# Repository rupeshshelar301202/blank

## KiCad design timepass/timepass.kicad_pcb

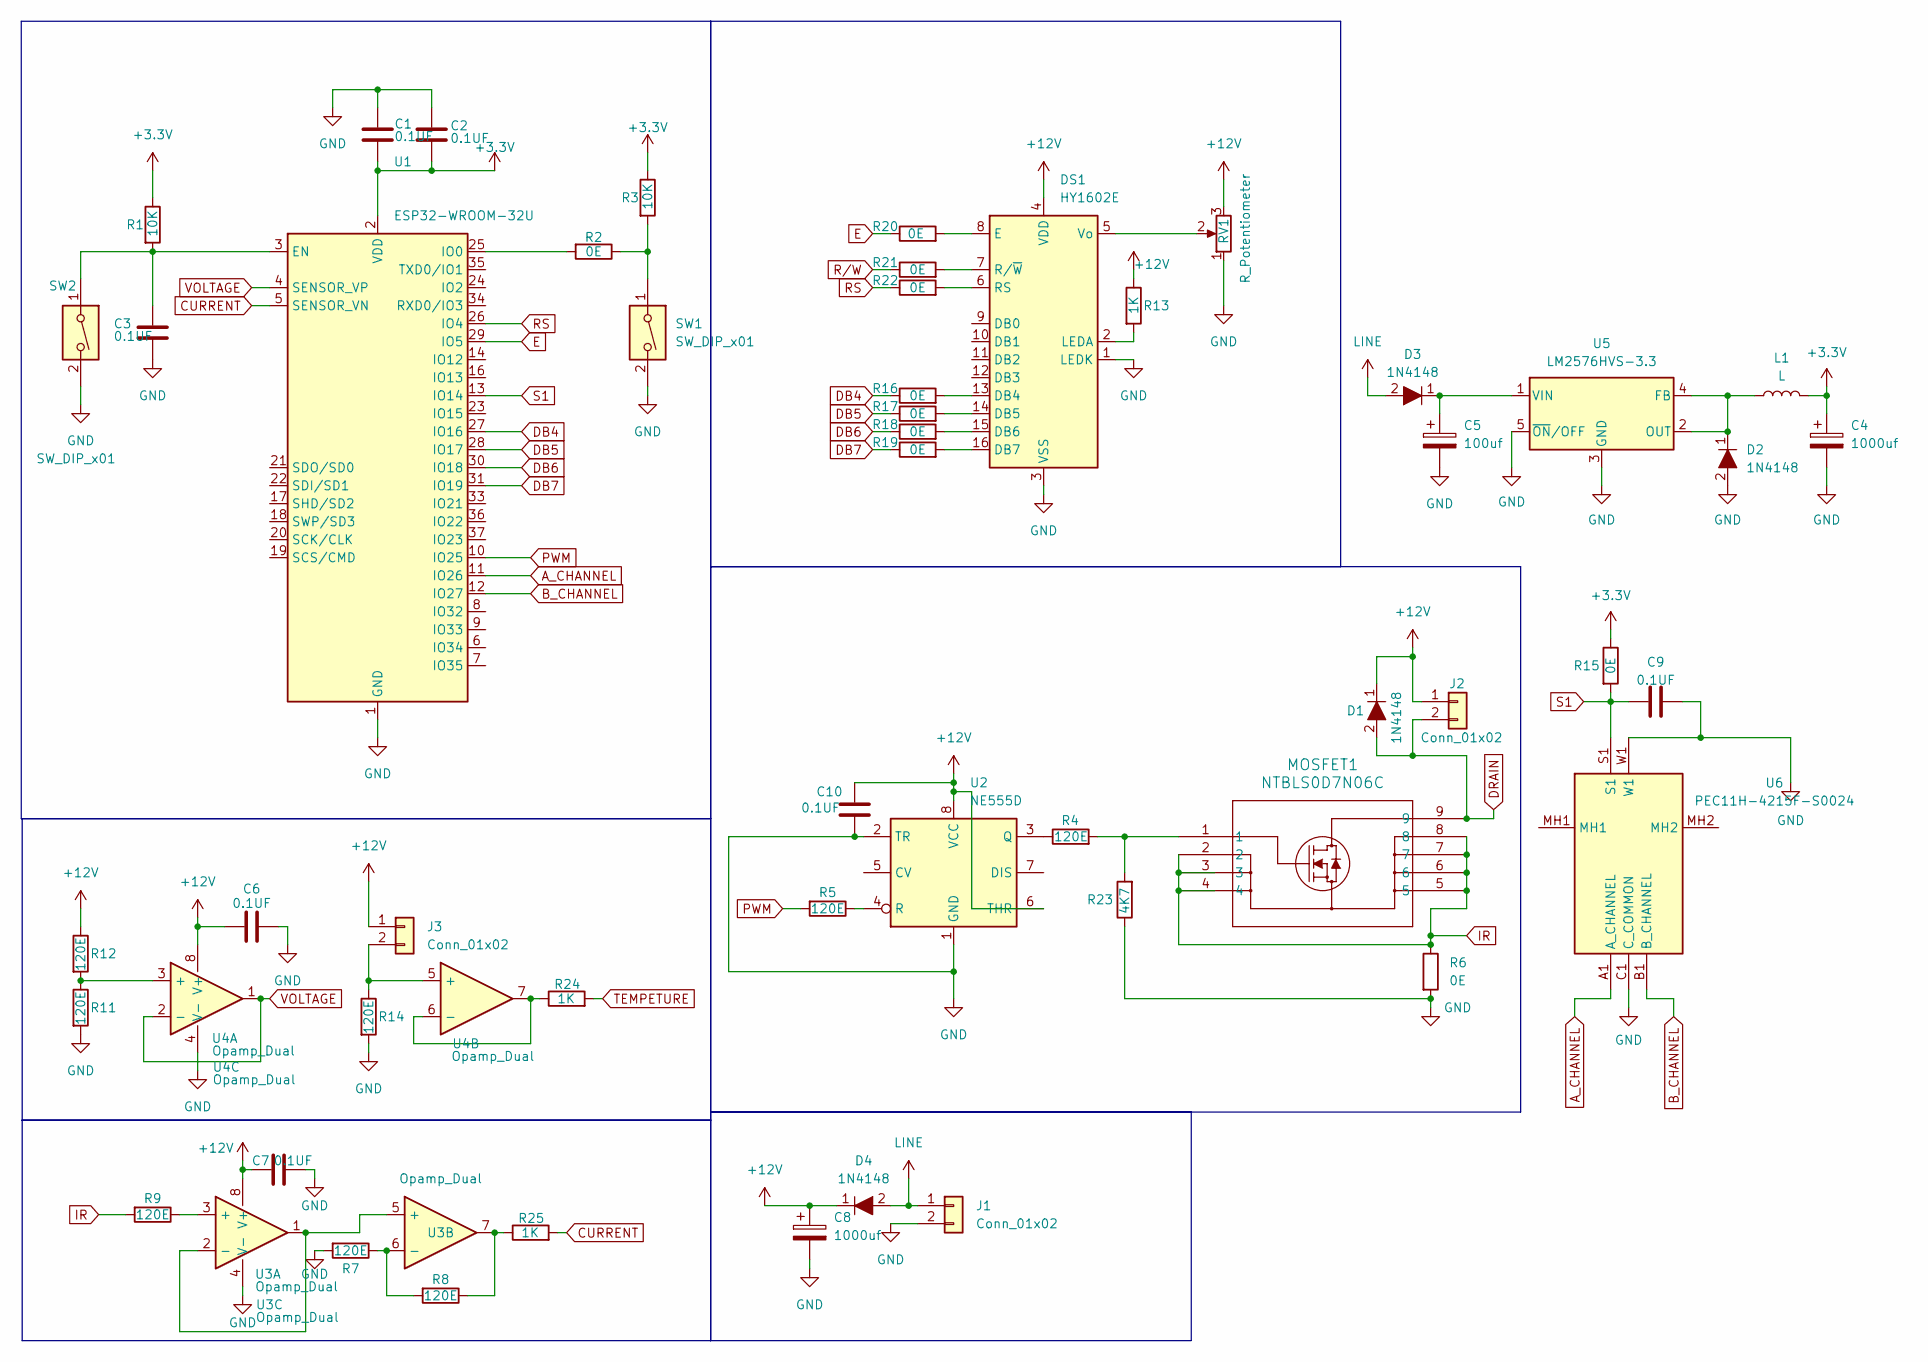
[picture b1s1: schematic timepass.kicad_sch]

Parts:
C1, C2, C3, C6, C7, C9, C10: 0.1UF; C_Disc_D8.0mm_W5.0mm_P10.00mm
C4, C8: 1000uf; CP_Radial_D12.5mm_P7.50mm
C5: 100uf; CP_Radial_D10.0mm_P5.00mm
D1, D2, D3, D4: 1N4148; D_A-405_P7.62mm_Horizontal; MPN 1N4148; Digi-Key_PN 1N4148FS-ND
DS1: HY1602E
J1, J2, J3: Conn_01x02; TerminalBlock_Phoenix_MKDS-1,5-2-5.08_1x02_P5.08mm_Horizont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
L1: L; L_Coilcraft_MSS1278-XXX
MOSFET1: NTBLS0D7N06C; H-PSOF8L_100CU_ONS
R1, R3: 10K; 1_4W RES
R2, R6, R15, R16, R17, R18, R19, R20, R21, R22: 0E; 1_4W RES
R4, R5, R7, R8, R9, R11, R12, R14: 120E; 1_4W RES
R13, R24, R25: 1K; 1_4W RES
R23: 4K7; 1_4W RES
RV1: R_Potentiometer; Potentiometer_Bourns_3386C_Horizontal
SW1, SW2: SW_DIP_x01; SW_PUSH_6mm_H7.3mm_THT
U1: ESP32-WROOM-32U
U2: NE555D; DIP-8_W7.62mm_LongPads
U3, U4: Opamp_Dual; DIP-8_W7.62mm
U5: LM2576HVS-3.3; TO-263-5_TabPin3
U6: PEC11H-4215F-S0024; PEC11H4215FS0024; Mouser Part Number 652-PEC11H4215FS0024

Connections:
+3.3V: C1.2, C2.2, C4.1, L1.2, R1.1, R3.1, R15.1, U1.2 (VDD)
+12V: C6.1, C7.1, C8.1, C10.2, D1.1, D4.1, DS1.4 (VDD), J2.1, J3.1, R12.1, R13.1, RV1.3, U2.6 (THR), U2.8 (VCC), U3.8 (V+), U4.8 (V+)
A_CHANNEL: U1.11 (IO26), U6.A1 (A_CHANNEL)
B_CHANNEL: U1.12 (IO27), U6.B1 (B_CHANNEL)
CURRENT: R25.2, U1.5 (SENSOR_VN)
DB4: R16.1, U1.27 (IO16)
DB5: R17.1, U1.28 (IO17)
DB6: R18.1, U1.30 (IO18)
DB7: R19.1, U1.31 (IO19)
DRAIN: D1.2, J2.2, MOSFET1.9
E: R20.1, U1.29 (IO5)
GND: C1.1, C2.1, C3.2, C4.2, C5.2, C6.2, C7.2, C8.2, C9.2, C10.1, D2.2, DS1.1 (LEDK), DS1.3 (VSS), J1.2, R6.2, R7.2, R11.2, R14.2, R23.1, RV1.1, SW1.2, SW2.2, U1.1 (GND), U1.15 (GND), U1.38 (GND), U1.39 (GND), U2.1 (GND), U2.2 (TR), U3.4 (V-), U4.4 (V-), U5.3 (GND), U5.5 (~ON/OFF), U6.C1 (C_COMMON), U6.W1
IR: MOSFET1.2, MOSFET1.3, MOSFET1.4, MOSFET1.5, MOSFET1.6, MOSFET1.7, MOSFET1.8, R6.1, R9.2
LINE: D3.2, D4.2, J1.1
unnamed: DS1.13 (DB4), R16.2
unnamed: DS1.14 (DB5), R17.2
unnamed: DS1.15 (DB6), R18.2
unnamed: DS1.16 (DB7), R19.2
unnamed: DS1.8 (E), R20.2
unnamed: DS1.2 (LEDA), R13.2
unnamed: DS1.6 (RS), R22.2
unnamed: DS1.7 (R/~W), R21.2
unnamed: DS1.5 (Vo), RV1.2
unnamed: J3.2, R14.1, U4.5 (+)
unnamed: MOSFET1.1, R4.2, R23.2
unnamed: R2.1, R3.2, SW1.1
unnamed: R8.1, R25.1, U3.7
unnamed: C3.1, R1.2, SW2.1, U1.3 (EN)
unnamed: R2.2, U1.25 (IO0)
unnamed: R4.1, U2.3 (Q)
unnamed: R5.1, U2.4 (R)
unnamed: R9.1, U3.3 (+)
unnamed: U3.1, U3.2 (-), U3.5 (+)
unnamed: R7.1, R8.2, U3.6 (-)
unnamed: R11.1, R12.2, U4.3 (+)
unnamed: R24.1, U4.6 (-), U4.7
unnamed: D2.1, L1.1, U5.2 (OUT), U5.4 (FB)
unnamed: C5.1, D3.1, U5.1 (VIN)
PWM: R5.2, U1.10 (IO25)
RS: R22.1, U1.26 (IO4)
R/W: R21.1
S1: C9.1, R15.2, U1.13 (IO14), U6.S1
TEMPETURE: R24.2
VOLTAGE: U1.4 (SENSOR_VP), U4.1, U4.2 (-)

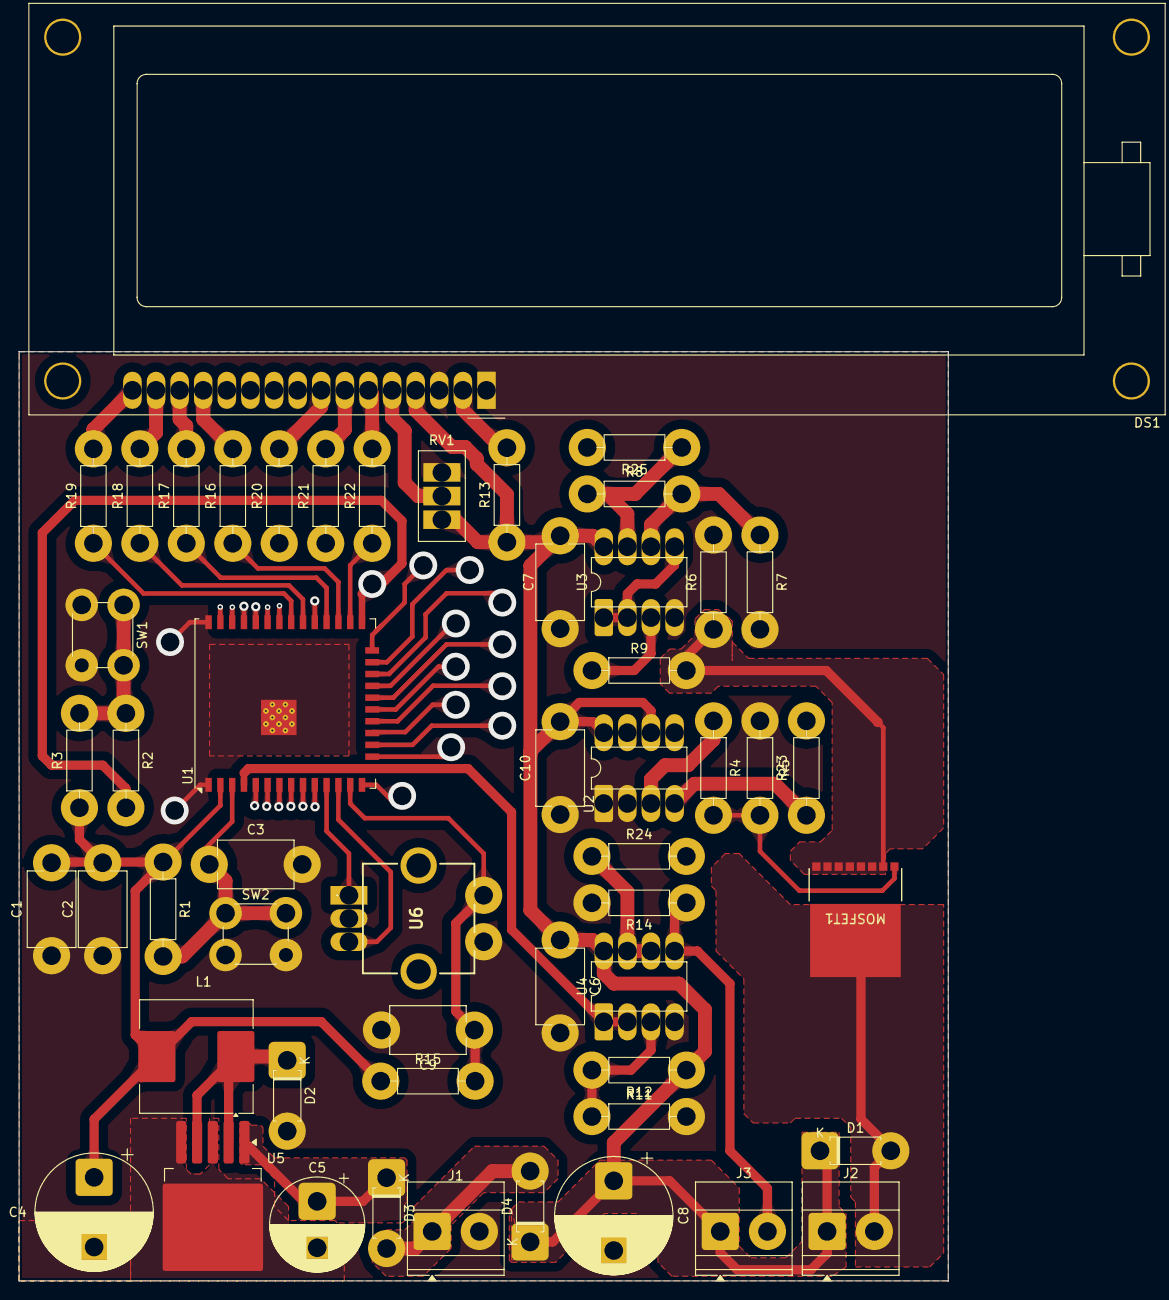
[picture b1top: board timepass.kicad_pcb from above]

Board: 2 copper layers, 100.0 x 100.0 mm, 53 parts (0 on the bottom side), 42 nets.

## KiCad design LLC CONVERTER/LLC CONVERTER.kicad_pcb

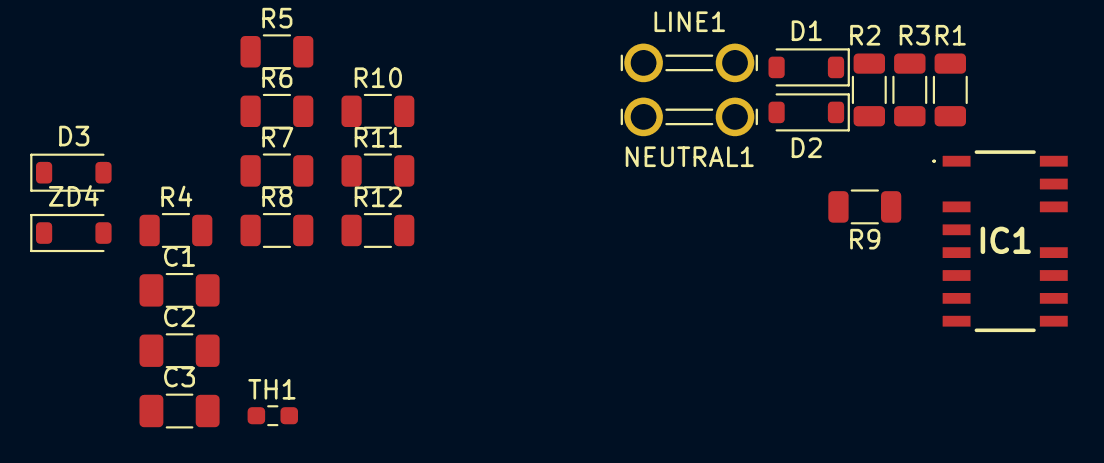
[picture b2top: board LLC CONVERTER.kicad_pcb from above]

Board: 2 copper layers, 23 parts (0 on the bottom side), 18 nets, no tracks yet.

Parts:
C1: 100NF/100V; C_1206_3216Metric_Pad1.33x1.80mm_HandSolder
C2, C3: 1NF/100V; C_1206_3216Metric_Pad1.33x1.80mm_HandSolder
D1, D2, D3: 1N4148W; D_SOD-123
IC1: UCC256601DDBR
LINE1: SPADE; TE_62409-1
NEUTRAL1: SPADE; TE_62409-1
R1, R2, R3: 1K65; R_1206_3216Metric
R4: 2E2; R_1206_3216Metric
R5: 560K; R_1206_3216Metric
R6: 150K; R_1206_3216Metric
R7, R8, R9: 3M3; R_1206_3216Metric
R10: 35K7; R_1206_3216Metric
R11, R12: 15K; R_1206_3216Metric
TH1: B57371V2474J060; R_0603_1608Metric_Pad0.98x0.95mm_HandSolder
ZD4: 15V; D_SOD-123

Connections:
BLK: C3.1, IC1.3 (BLK), R9.1, R10.2
GNDPWR: C2.2, C3.2, IC1.10 (GNDP), R6.1, R10.1, R12.1, TH1.2
HS: C1.1, IC1.16 (HS)
LL: C2.1, IC1.6 (LL), R5.2, R6.2
unnamed: D1.2 (A), LINE1.1
unnamed: D1.1 (K), D2.1 (K), R3.1
unnamed: D2.2 (A), NEUTRAL1.1
unnamed: D3.2 (A), R4.1
unnamed: C1.2, D3.1 (K), IC1.14 (HB)
unnamed: IC1.1 (HV), R1.2
unnamed: R1.1, R2.2
unnamed: R2.1, R3.2
unnamed: R7.1, R8.2
unnamed: R8.1, R9.2
unnamed: R11.1, ZD4.1 (K)
OVP: IC1.4 (OVP/OTP), R12.2, TH1.1, ZD4.2 (A)
V5P: IC1.8 (V5P), R5.1
VCC: IC1.12 (VCCP), R4.2, R11.2

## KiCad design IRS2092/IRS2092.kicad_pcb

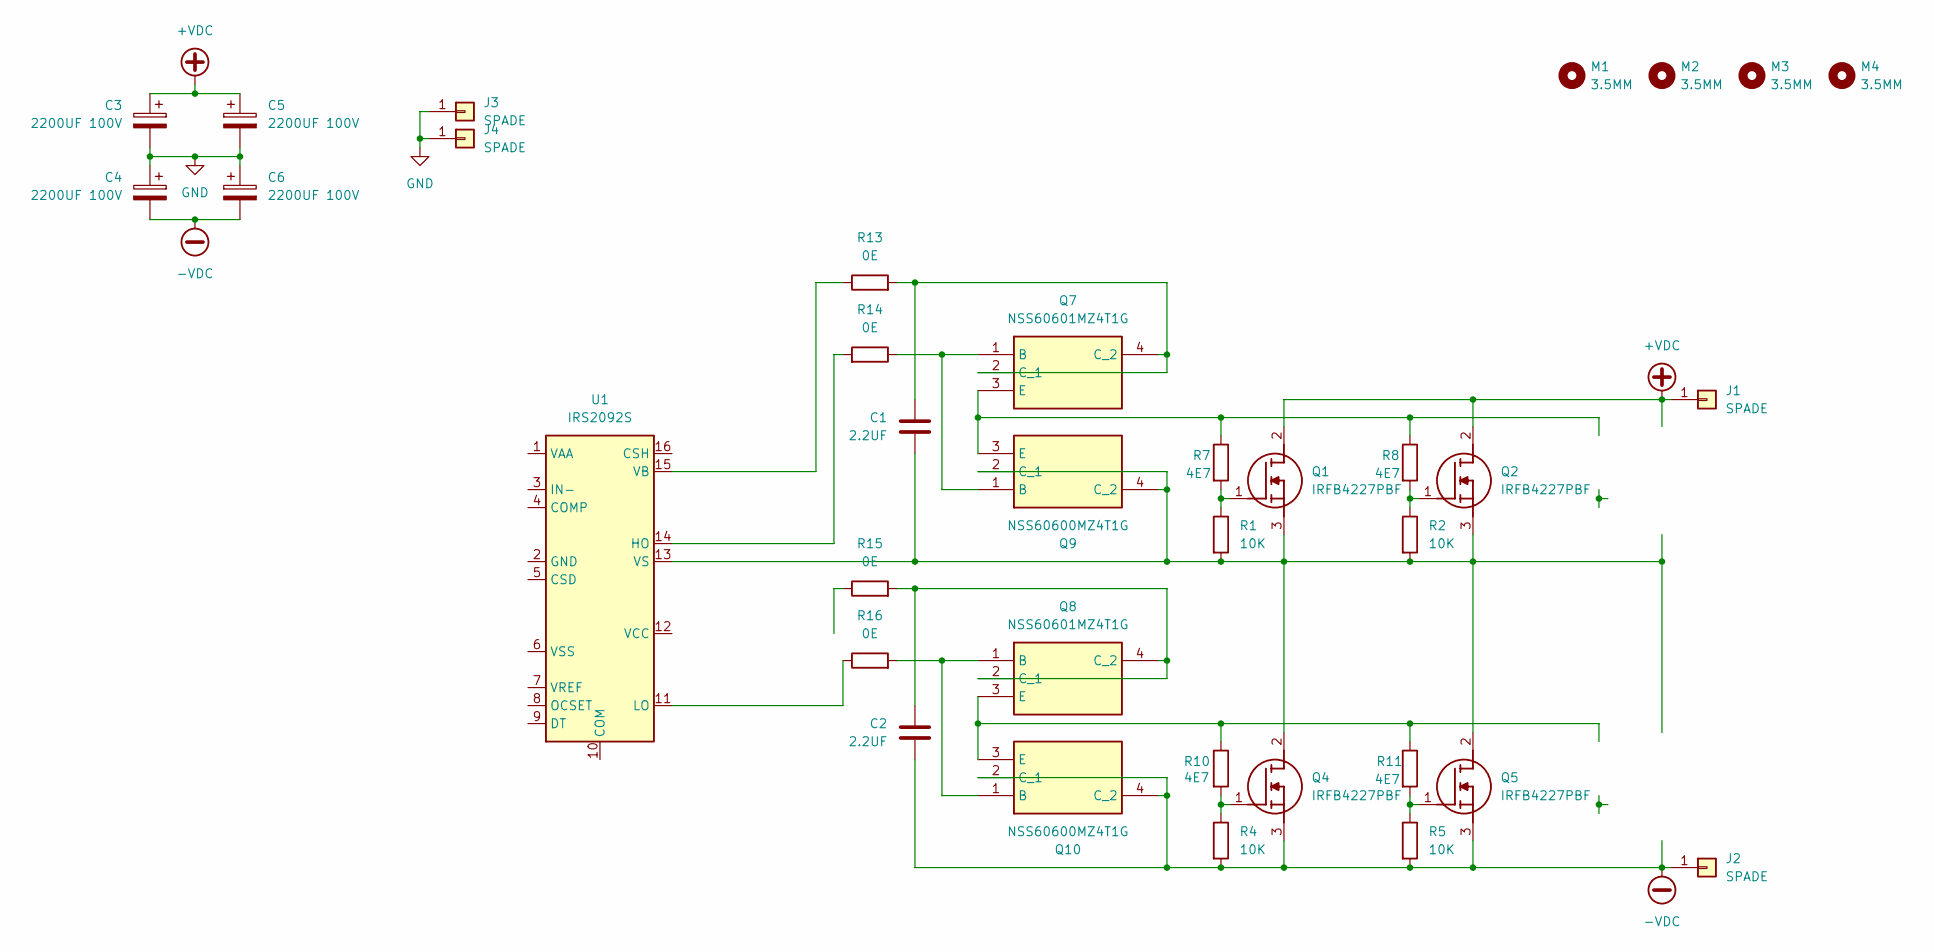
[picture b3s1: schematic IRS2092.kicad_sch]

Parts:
C1, C2: 2.2UF; C_1206_3216Metric_Pad1.33x1.80mm_HandSolder
C3, C4, C5, C6: 2200UF 100V; CP_Radial_D30.0mm_P10.00mm_SnapIn
J1, J2, J3, J4: SPADE; TE_62409-1
M1, M2, M3, M4: 3.5MM; MountingHole_3.5mm_Pad_Via
Q1, Q2, Q4, Q5: IRFB4227PBF; TO-220-3_Horizontal_TabUp; Manufacturer_Part_Number IRFB4227PBF; Mouser Part Number 942-IRFB4227PBF
Q7, Q8: NSS60601MZ4T1G; SOT230P700X175-4N; Manufacturer_Part_Number NSS60601MZ4T1G; Mouser Part Number 863-NSS60601MZ4T1G
Q9, Q10: NSS60600MZ4T1G; SOT230P700X175-4N; Manufacturer_Part_Number NSS60600MZ4T1G; Mouser Part Number 863-NSS60600MZ4T1G
R1, R2, R4, R5: 10K; R_1206_3216Metric_Pad1.30x1.75mm_HandSolder
R7, R8, R10, R11: 4E7; R_1206_3216Metric_Pad1.30x1.75mm_HandSolder
R13, R14, R15, R16: 0E; R_1206_3216Metric_Pad1.30x1.75mm_HandSolder
U1: IRS2092S; SOIC-16_3.9x9.9mm_P1.27mm

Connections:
+VDC: C3.1, C5.1, J1.1, Q1.2 (D), Q2.2 (D)
-VDC: C2.2, C4.2, C6.2, J2.1, Q4.3 (S), Q5.3 (S), Q10.2 (C_1), Q10.4 (C_2), R4.2, R5.2
GND: C3.2, C4.1, C5.2, C6.1, J3.1, J4.1
unnamed: Q1.1 (G), R1.1, R7.2
unnamed: C1.2, Q1.3 (S), Q2.3 (S), Q4.2 (D), Q5.2 (D), Q9.2 (C_1), Q9.4 (C_2), R1.2, R2.2, U1.13 (VS)
unnamed: Q2.1 (G), R2.1, R8.2
unnamed: Q4.1 (G), R4.1, R10.2
unnamed: Q5.1 (G), R5.1, R11.2
unnamed: Q7.1 (B), Q9.1 (B), R14.1
unnamed: C1.1, Q7.2 (C_1), Q7.4 (C_2), R13.2
unnamed: Q7.3 (E), Q9.3 (E), R7.1, R8.1
unnamed: C2.1, Q8.2 (C_1), Q8.4 (C_2), R15.2
unnamed: Q8.1 (B), Q10.1 (B), R16.2
unnamed: Q8.3 (E), Q10.3 (E), R10.1, R11.1
unnamed: R14.2, U1.14 (HO)
unnamed: R16.1, U1.11 (LO)
unnamed: R13.1, U1.15 (VB)

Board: 2 copper layers, 35 parts (4 on the bottom side), 17 nets, no tracks yet.

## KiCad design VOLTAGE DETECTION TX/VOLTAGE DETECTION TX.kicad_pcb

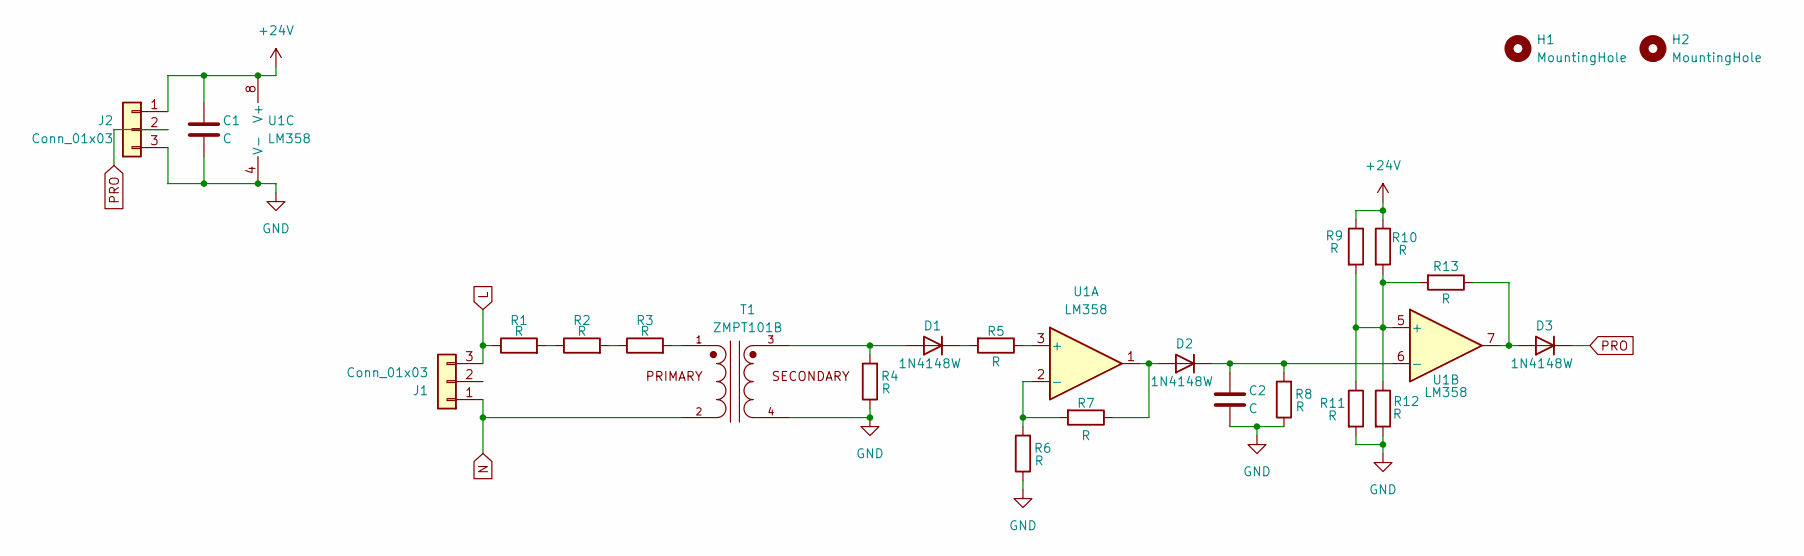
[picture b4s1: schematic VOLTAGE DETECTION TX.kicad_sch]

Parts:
C1, C2: C; C_1206_3216Metric_Pad1.33x1.80mm_HandSolder
D1, D2, D3: 1N4148W; D_SOD-123
H1, H2: MountingHole; MountingHole_3.2mm_M3_Pad_Via
J1: Conn_01x03; JST_VH_B3P-VH-B_1x03_P3.96mm_Vertical
J2: Conn_01x03; Molex_KK-254_AE-6410-03A_1x03_P2.54mm_Vertical
R1, R2, R3, R4: R; R_1206_3216Metric_Pad1.30x1.75mm_HandSolder
R5, R6, R7, R8, R9, R10, R11, R12, R13: R; R_0603_1608Metric_Pad0.98x0.95mm_HandSolder
T1: ZMPT101B; XFMR_ZMPT101B; PARTREV NA
U1: LM358; SOIC-8_3.9x4.9mm_P1.27mm

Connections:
+24V: C1.1, J2.1, R9.1, R10.1, U1.8 (V+)
GND: C1.2, C2.2, J2.3, R4.1, R6.1, R8.1, R11.2, R12.2, T1.4, U1.4 (V-)
L: J1.3, R1.1
N: J1.1, T1.2
unnamed: D1.2 (A), R4.2, T1.3
unnamed: D1.1 (K), R5.2
unnamed: D2.2 (A), R7.1, U1.1
unnamed: C2.1, D2.1 (K), R8.2, U1.6 (-)
unnamed: D3.2 (A), R13.1, U1.7
unnamed: R1.2, R2.1
unnamed: R2.2, R3.1
unnamed: R3.2, T1.1
unnamed: R5.1, U1.3 (+)
unnamed: R6.2, R7.2, U1.2 (-)
unnamed: R9.2, R10.2, R11.1, R12.1, R13.2, U1.5 (+)
PRO: D3.1 (K), J2.2

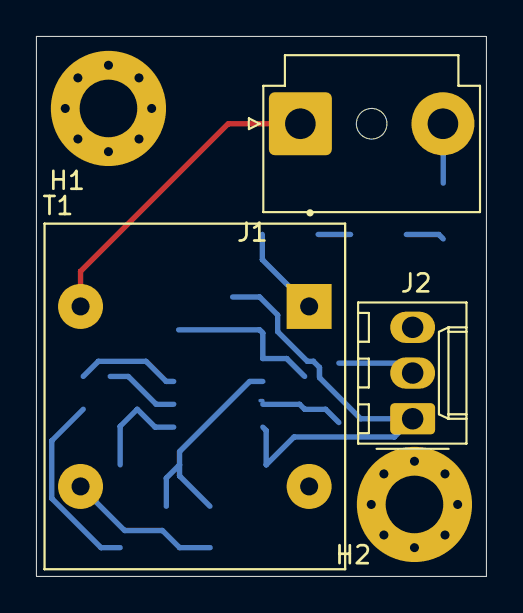
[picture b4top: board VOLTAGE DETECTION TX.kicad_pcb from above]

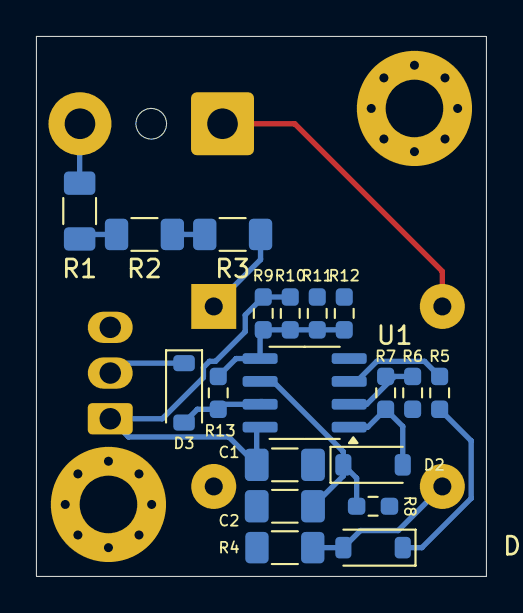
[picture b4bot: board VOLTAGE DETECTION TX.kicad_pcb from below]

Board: 2 copper layers, 25.0 x 30.0 mm, 24 parts (19 on the bottom side), 16 nets.

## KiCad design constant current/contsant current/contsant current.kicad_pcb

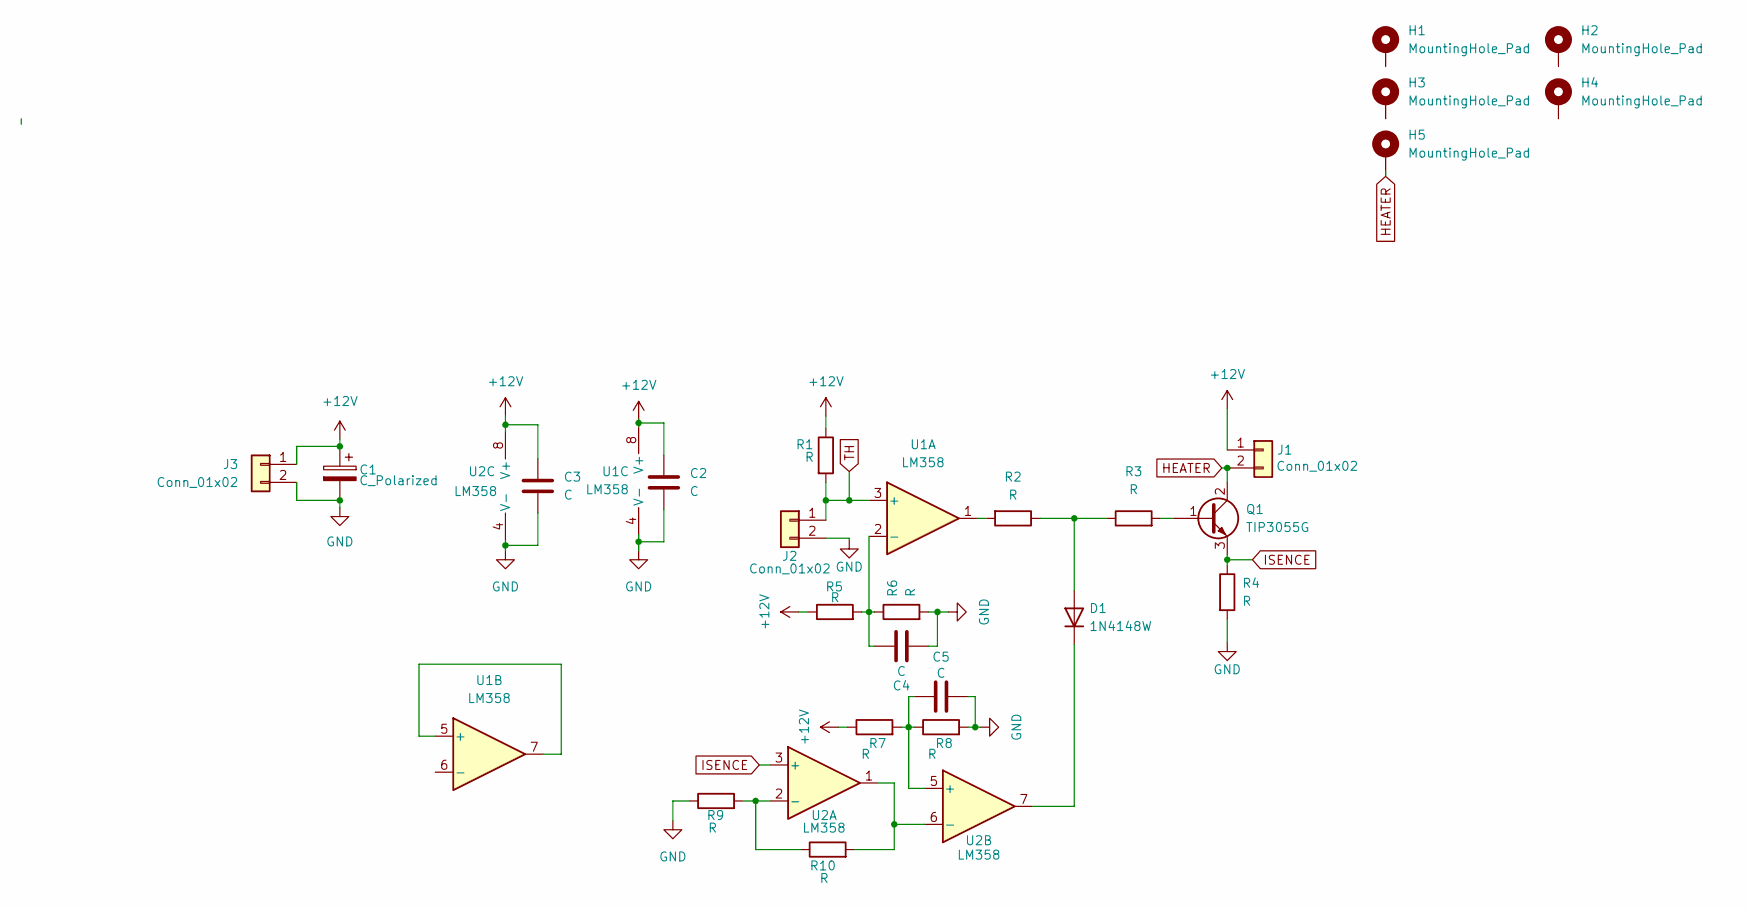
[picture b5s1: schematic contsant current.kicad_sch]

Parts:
C1: C_Polarized
C2, C3, C4, C5: C; C_1206_3216Metric_Pad1.33x1.80mm_HandSolder
D1: 1N4148W; D_SOD-123
H1, H2, H3, H4, H5: MountingHole_Pad; MountingHole_3.5mm_Pad_Via
J1, J2, J3: Conn_01x02; TerminalBlock_Phoenix_MKDS-1,5-2-5.08_1x02_P5.08mm_Horizont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
Q1: TIP3055G; TO-247-3_Horizontal_TabDown
R1, R2, R3, R4, R5, R6, R7, R8, R9, R10: R; R_1206_3216Metric_Pad1.30x1.75mm_HandSolder
U1, U2: LM358; SOIC-8_3.9x4.9mm_P1.27mm

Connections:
+12V: C1.1, C2.1, C3.1, J1.1, J3.1, R1.1, R5.1, R7.1, U1.8 (V+), U2.8 (V+)
GND: C1.2, C2.2, C3.2, C4.1, C5.2, J2.2, J3.2, R4.2, R6.2, R8.2, R9.1, U1.4 (V-), U2.4 (V-)
HEATER: H5.1, J1.2, Q1.2 (C)
ISENCE: Q1.3 (E), R4.1, U2.3 (+)
unnamed: D1.2 (A), R2.1, R3.1
unnamed: D1.1 (K), U2.7
unnamed: Q1.1 (B), R3.2
unnamed: R2.2, U1.1
unnamed: C4.2, R5.2, R6.1, U1.2 (-)
unnamed: U1.5 (+), U1.7
unnamed: R9.2, R10.1, U2.2 (-)
unnamed: C5.1, R7.2, R8.1, U2.5 (+)
unnamed: R10.2, U2.1, U2.6 (-)
TH: J2.1, R1.2, U1.3 (+)

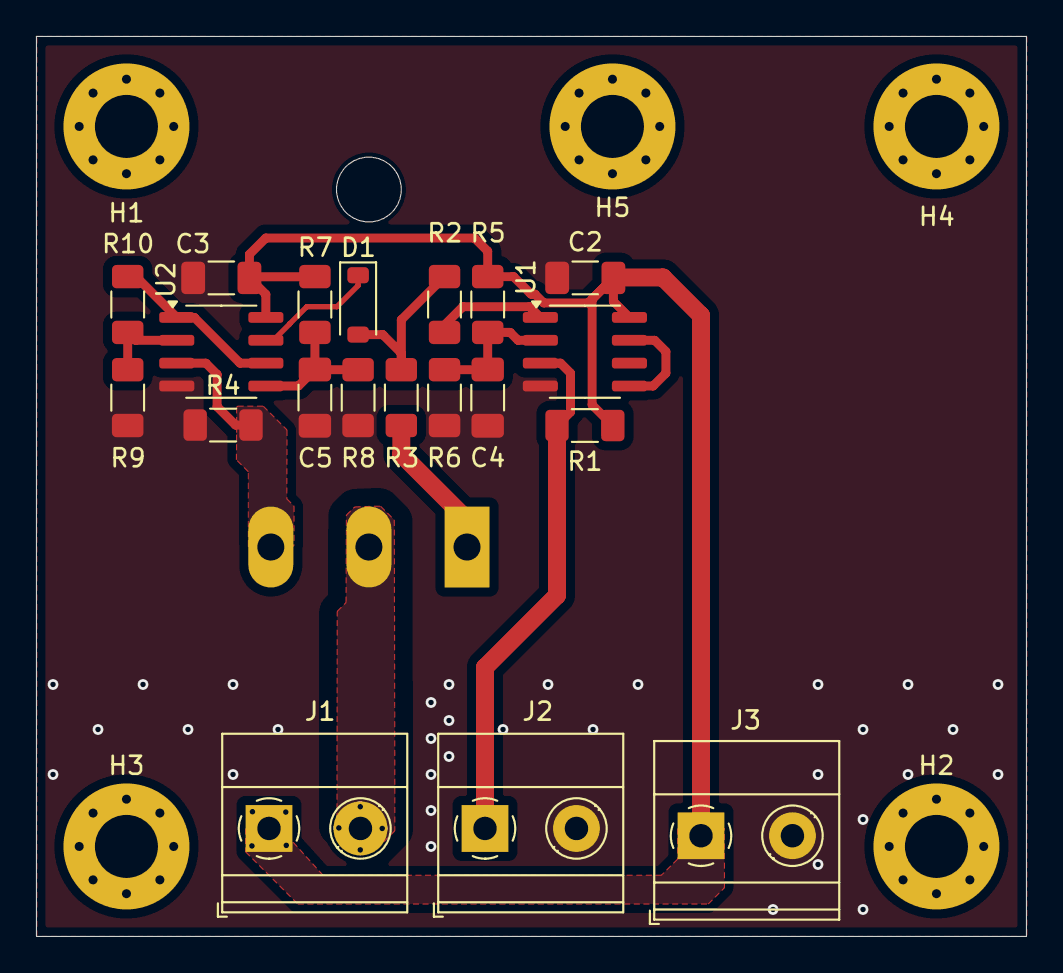
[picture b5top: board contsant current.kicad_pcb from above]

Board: 2 copper layers, 55.0 x 50.0 mm, 26 parts (1 on the bottom side), 14 nets.

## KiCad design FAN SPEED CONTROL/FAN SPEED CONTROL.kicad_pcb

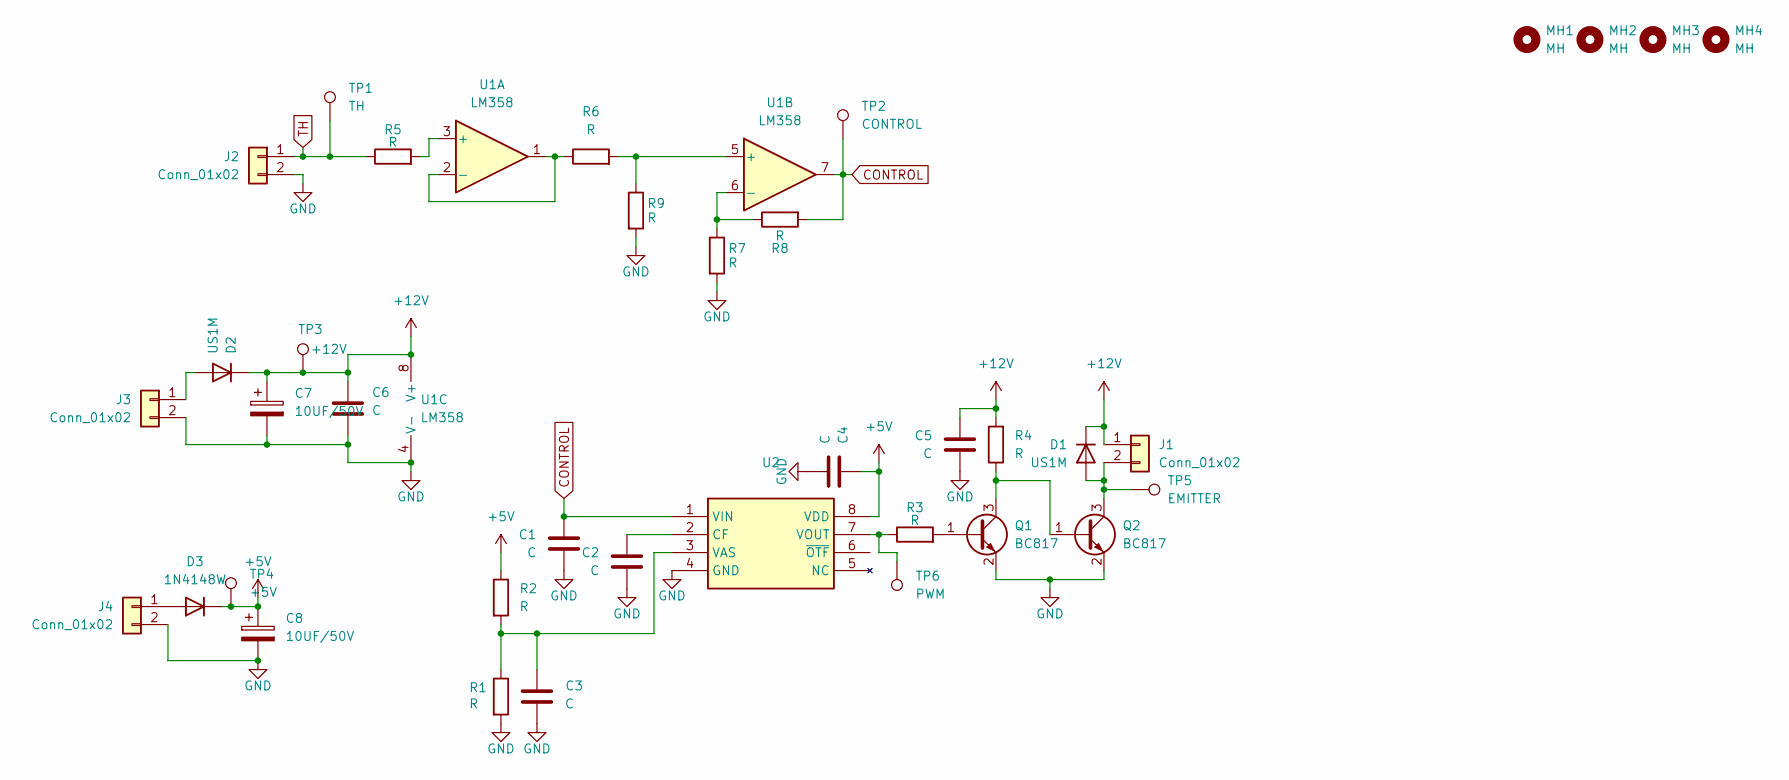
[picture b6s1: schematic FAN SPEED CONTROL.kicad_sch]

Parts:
C1, C2, C3, C4, C5: C; C_0603_1608Metric_Pad1.08x0.95mm_HandSolder
C6: C; C_1206_3216Metric_Pad1.33x1.80mm_HandSolder
C7, C8: 10UF/50V; CP_Radial_D5.0mm_P2.00mm
D1, D2: US1M; D_SMA
D3: 1N4148W; D_SOD-123
J1, J2, J3, J4: Conn_01x02; Molex_KK-254_AE-6410-02A_1x02_P2.54mm_Vertical
MH1, MH2, MH3, MH4: MH; MountingHole_3.5mm_Pad_Via
Q1, Q2: BC817; SOT-23
R1, R2, R3, R4, R5, R6, R7, R8, R9: R; R_0603_1608Metric_Pad0.98x0.95mm_HandSolder
TP1: TH; TestPoint_Pad_D3.0mm
TP2: CONTROL; TestPoint_Pad_D3.0mm
TP3: +12V; TestPoint_Pad_D3.0mm
TP4: +5V; TestPoint_Pad_D3.0mm
TP5: EMITTER; TestPoint_Pad_D3.0mm
TP6: PWM; TestPoint_Pad_D3.0mm
U1: LM358; SOIC-8_3.9x4.9mm_P1.27mm
U2: TC648BEOA; SOIC127P600X175-8N; Manufacturer_Part_Number TC648BEOA; Mouser Part Number 579-TC648BEOA

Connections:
+5V: C4.1, C8.1, D3.1 (K), R2.1, TP4.1, U2.8 (VDD)
+12V: C5.1, C6.1, C7.1, D1.1 (K), D2.1 (K), J1.1, R4.2, TP3.1, U1.8 (V+)
CONTROL: C1.1, R8.2, TP2.1, U1.7, U2.1 (VIN)
GND: C1.2, C2.2, C3.2, C4.2, C5.2, C6.2, C7.2, C8.2, J2.2, J3.2, J4.2, Q1.2 (E), Q2.2 (E), R1.2, R7.2, R9.2, U1.4 (V-), U2.4 (GND)
unnamed: D1.2 (A), J1.2, Q2.3 (C), TP5.1
unnamed: D2.2 (A), J3.1
unnamed: D3.2 (A), J4.1
unnamed: Q1.1 (B), R3.2
unnamed: Q1.3 (C), Q2.1 (B), R4.1
unnamed: R5.2, U1.3 (+)
unnamed: R6.1, U1.1, U1.2 (-)
unnamed: R6.2, R9.1, U1.5 (+)
unnamed: R7.1, R8.1, U1.6 (-)
unnamed: C2.1, U2.2 (CF)
unnamed: C3.1, R1.1, R2.2, U2.3 (VAS)
unnamed: R3.1, TP6.1, U2.7 (VOUT)
TH: J2.1, R5.1, TP1.1

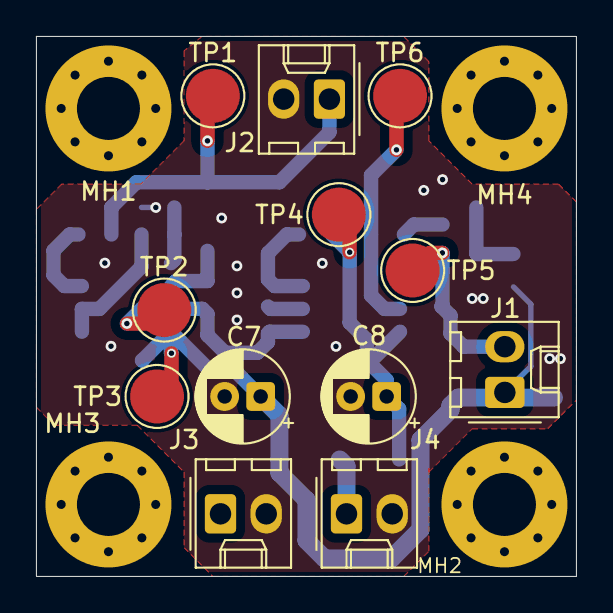
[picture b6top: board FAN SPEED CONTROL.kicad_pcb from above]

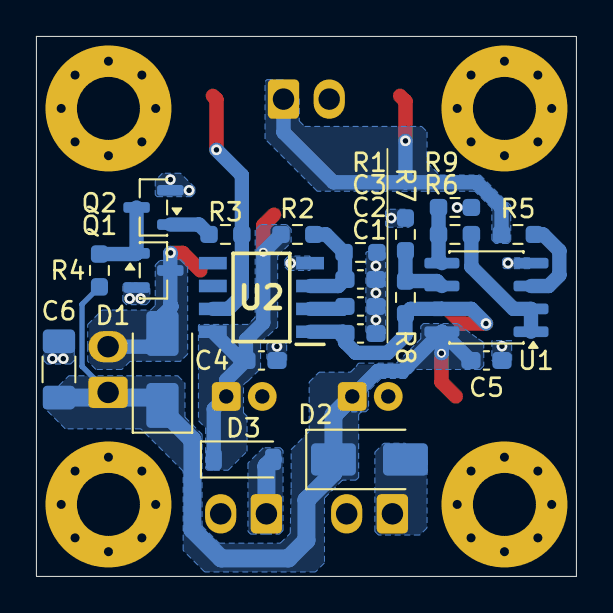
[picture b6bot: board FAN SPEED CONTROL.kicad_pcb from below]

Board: 2 copper layers, 30.0 x 30.0 mm, 38 parts (22 on the bottom side), 17 nets.
